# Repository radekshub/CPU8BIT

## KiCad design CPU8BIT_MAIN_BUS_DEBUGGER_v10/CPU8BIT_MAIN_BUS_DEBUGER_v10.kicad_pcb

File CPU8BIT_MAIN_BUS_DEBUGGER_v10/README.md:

CPU 8 bit - MAIN BUS DEBUGGER version 1.0

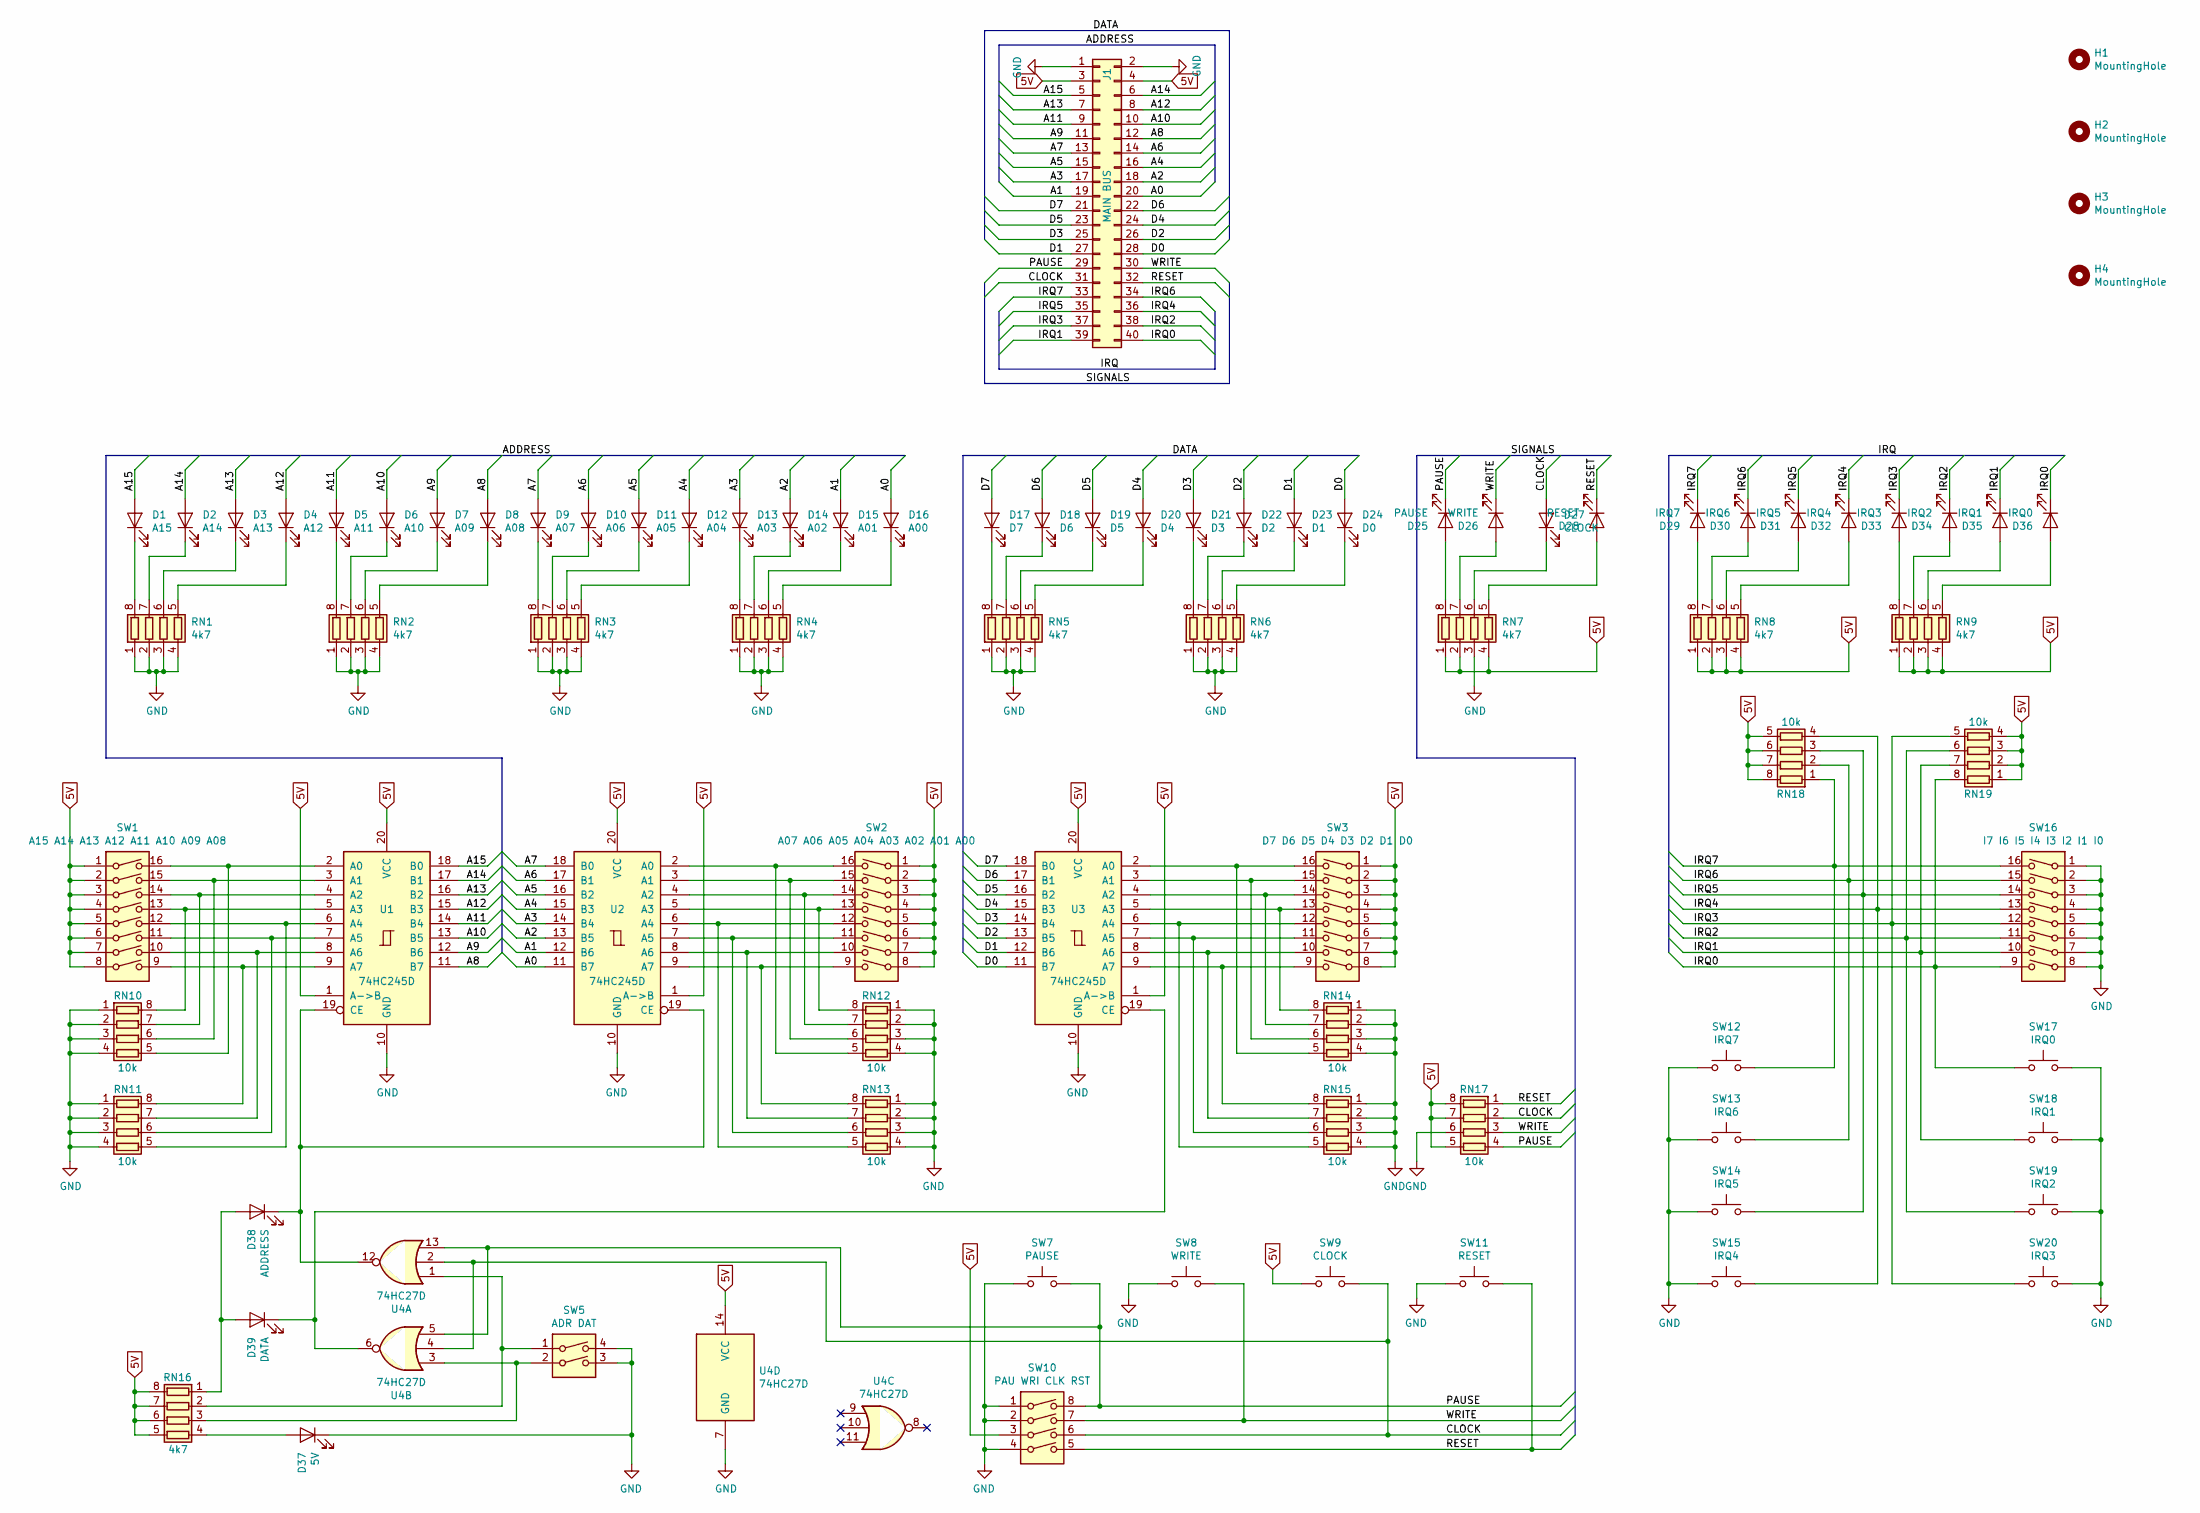
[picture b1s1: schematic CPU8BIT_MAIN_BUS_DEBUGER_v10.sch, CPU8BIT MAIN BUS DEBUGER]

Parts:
D1: A15; LED_0805_2012Metric_Pad1.15x1.40mm_HandSolder
D2: A14; LED_0805_2012Metric_Pad1.15x1.40mm_HandSolder
D3: A13; LED_0805_2012Metric_Pad1.15x1.40mm_HandSolder
D4: A12; LED_0805_2012Metric_Pad1.15x1.40mm_HandSolder
D5: A11; LED_0805_2012Metric_Pad1.15x1.40mm_HandSolder
D6: A10; LED_0805_2012Metric_Pad1.15x1.40mm_HandSolder
D7: A09; LED_0805_2012Metric_Pad1.15x1.40mm_HandSolder
D8: A08; LED_0805_2012Metric_Pad1.15x1.40mm_HandSolder
D9: A07; LED_0805_2012Metric_Pad1.15x1.40mm_HandSolder
D10: A06; LED_0805_2012Metric_Pad1.15x1.40mm_HandSolder
D11: A05; LED_0805_2012Metric_Pad1.15x1.40mm_HandSolder
D12: A04; LED_0805_2012Metric_Pad1.15x1.40mm_HandSolder
D13: A03; LED_0805_2012Metric_Pad1.15x1.40mm_HandSolder
D14: A02; LED_0805_2012Metric_Pad1.15x1.40mm_HandSolder
D15: A01; LED_0805_2012Metric_Pad1.15x1.40mm_HandSolder
D16: A00; LED_0805_2012Metric_Pad1.15x1.40mm_HandSolder
D17: D7; LED_0805_2012Metric_Pad1.15x1.40mm_HandSolder
D18: D6; LED_0805_2012Metric_Pad1.15x1.40mm_HandSolder
D19: D5; LED_0805_2012Metric_Pad1.15x1.40mm_HandSolder
D20: D4; LED_0805_2012Metric_Pad1.15x1.40mm_HandSolder
D21: D3; LED_0805_2012Metric_Pad1.15x1.40mm_HandSolder
D22: D2; LED_0805_2012Metric_Pad1.15x1.40mm_HandSolder
D23: D1; LED_0805_2012Metric_Pad1.15x1.40mm_HandSolder
D24: D0; LED_0805_2012Metric_Pad1.15x1.40mm_HandSolder
D25: PAUSE; LED_0805_2012Metric_Pad1.15x1.40mm_HandSolder
D26: WRITE; LED_0805_2012Metric_Pad1.15x1.40mm_HandSolder
D27: CLOCK; LED_0805_2012Metric_Pad1.15x1.40mm_HandSolder
D28: RESET; LED_0805_2012Metric_Pad1.15x1.40mm_HandSolder
D29: IRQ7; LED_0805_2012Metric_Pad1.15x1.40mm_HandSolder
D30: IRQ6; LED_0805_2012Metric_Pad1.15x1.40mm_HandSolder
D31: IRQ5; LED_0805_2012Metric_Pad1.15x1.40mm_HandSolder
D32: IRQ4; LED_0805_2012Metric_Pad1.15x1.40mm_HandSolder
D33: IRQ3; LED_0805_2012Metric_Pad1.15x1.40mm_HandSolder
D34: IRQ2; LED_0805_2012Metric_Pad1.15x1.40mm_HandSolder
D35: IRQ1; LED_0805_2012Metric_Pad1.15x1.40mm_HandSolder
D36: IRQ0; LED_0805_2012Metric_Pad1.15x1.40mm_HandSolder
D37: 5V; LED_0805_2012Metric_Pad1.15x1.40mm_HandSolder
D38: ADDRESS; LED_0805_2012Metric_Pad1.15x1.40mm_HandSolder
D39: DATA; LED_0805_2012Metric_Pad1.15x1.40mm_HandSolder
H1, H2, H3, H4: MountingHole; MountingHole_4.3mm_M4_Pad_Via
J1: MAIN BUS; PinHeader_2x20_P2.54mm_Horizontal
RN1, RN2, RN3, RN4, RN5, RN6, RN7, RN8, RN9, RN16: 4k7; R_Array_Convex_4x0603
RN10, RN11, RN12, RN13, RN14, RN15, RN17, RN18, RN19: 10k; R_Array_Convex_4x0603
SW1: A15 A14 A13 A12 A11 A10 A09 A08; SW_DIP_SPSTx08_Piano_10.8x21.88mm_W7.62mm_P2.54mm
SW2: A07 A06 A05 A04 A03 A02 A01 A00; SW_DIP_SPSTx08_Piano_10.8x21.88mm_W7.62mm_P2.54mm
SW3: D7 D6 D5 D4 D3 D2 D1 D0; SW_DIP_SPSTx08_Piano_10.8x21.88mm_W7.62mm_P2.54mm
SW5: ADR DAT; SW_DIP_SPSTx02_Piano_10.8x6.64mm_W7.62mm_P2.54mm
SW7: PAUSE; SW_PUSH_6mm
SW8: WRITE; SW_PUSH_6mm
SW9: CLOCK; SW_PUSH_6mm
SW10: PAU WRI CLK RST; SW_DIP_SPSTx04_Piano_10.8x11.72mm_W7.62mm_P2.54mm
SW11: RESET; SW_PUSH_6mm
SW12: IRQ7; SW_PUSH_6mm
SW13: IRQ6; SW_PUSH_6mm
SW14: IRQ5; SW_PUSH_6mm
SW15: IRQ4; SW_PUSH_6mm
SW16: I7 I6 I5 I4 I3 I2 I1 I0; SW_DIP_SPSTx08_Piano_10.8x21.88mm_W7.62mm_P2.54mm
SW17: IRQ0; SW_PUSH_6mm
SW18: IRQ1; SW_PUSH_6mm
SW19: IRQ2; SW_PUSH_6mm
SW20: IRQ3; SW_PUSH_6mm
U1, U2, U3: 74HC245D; SO-20_12.8x7.5mm_P1.27mm
U4: 74HC27D; SOIC-14_3.9x8.7mm_P1.27mm

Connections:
5V: J1.3, J1.4, RN7.1 (R1.1), RN7.2 (R2.1), RN7.4 (R4.1), RN8.1 (R1.1), RN8.2 (R2.1), RN8.3 (R3.1), RN8.4 (R4.1), RN9.1 (R1.1), RN9.2 (R2.1), RN9.3 (R3.1), RN9.4 (R4.1), RN16.5 (R4.2), RN16.6 (R3.2), RN16.7 (R2.2), RN16.8 (R1.2), RN17.5 (R4.2), RN17.7 (R2.2), RN17.8 (R1.2), RN18.5 (R4.2), RN18.6 (R3.2), RN18.7 (R2.2), RN18.8 (R1.2), RN19.1 (R1.1), RN19.2 (R2.1), RN19.3 (R3.1), RN19.4 (R4.1), SW1.1, SW1.2, SW1.3, SW1.4, SW1.5, SW1.6, SW1.7, SW1.8, SW2.1, SW2.2, SW2.3, SW2.4, SW2.5, SW2.6, SW2.7, SW2.8, SW3.1, SW3.2, SW3.3, SW3.4, SW3.5, SW3.6, SW3.7, SW3.8, SW9.1, SW10.3, U1.1 (A->B), U1.20 (VCC), U2.1 (A->B), U2.20 (VCC), U3.1 (A->B), U3.20 (VCC), U4.14 (VCC)
/A0: D16.2 (A), J1.20, U2.11 (B7)
/A1: D15.2 (A), J1.19, U2.12 (B6)
/A2: D14.2 (A), J1.18, U2.13 (B5)
/A3: D13.2 (A), J1.17, U2.14 (B4)
/A4: D12.2 (A), J1.16, U2.15 (B3)
/A5: D11.2 (A), J1.15, U2.16 (B2)
/A6: D10.2 (A), J1.14, U2.17 (B1)
/A7: D9.2 (A), J1.13, U2.18 (B0)
/A8: D8.2 (A), J1.12, U1.11 (B7)
/A9: D7.2 (A), J1.11, U1.12 (B6)
/A10: D6.2 (A), J1.10, U1.13 (B5)
/A11: D5.2 (A), J1.9, U1.14 (B4)
/A12: D4.2 (A), J1.8, U1.15 (B3)
/A13: D3.2 (A), J1.7, U1.16 (B2)
/A14: D2.2 (A), J1.6, U1.17 (B1)
/A15: D1.2 (A), J1.5, U1.18 (B0)
/CLOCK: D27.2 (A), J1.31, RN17.2 (R2.1), SW9.2, SW10.6, U4.2, U4.4
/D0: D24.2 (A), J1.28, U3.11 (B7)
/D1: D23.2 (A), J1.27, U3.12 (B6)
/D2: D22.2 (A), J1.26, U3.13 (B5)
/D3: D21.2 (A), J1.25, U3.14 (B4)
/D4: D20.2 (A), J1.24, U3.15 (B3)
/D5: D19.2 (A), J1.23, U3.16 (B2)
/D6: D18.2 (A), J1.22, U3.17 (B1)
/D7: D17.2 (A), J1.21, U3.18 (B0)
/IRQ0: D36.1 (K), J1.40, RN19.8 (R1.2), SW16.9, SW17.1
/IRQ1: D35.1 (K), J1.39, RN19.7 (R2.2), SW16.10, SW18.1
/IRQ2: D34.1 (K), J1.38, RN19.6 (R3.2), SW16.11, SW19.1
/IRQ3: D33.1 (K), J1.37, RN19.5 (R4.2), SW16.12, SW20.1
/IRQ4: D32.1 (K), J1.36, RN18.4 (R4.1), SW15.2, SW16.13
/IRQ5: D31.1 (K), J1.35, RN18.3 (R3.1), SW14.2, SW16.14
/IRQ6: D30.1 (K), J1.34, RN18.2 (R2.1), SW13.2, SW16.15
/IRQ7: D29.1 (K), J1.33, RN18.1 (R1.1), SW12.2, SW16.16
/PAUSE: D25.1 (K), J1.29, RN17.4 (R4.1), SW7.2, SW10.8, U4.5, U4.13
/RESET: D28.1 (K), J1.32, RN17.1 (R1.1), SW10.5, SW11.2
/WRITE: D26.1 (K), J1.30, RN17.3 (R3.1), SW8.2, SW10.7
GND: D37.1 (K), J1.1, J1.2, RN1.1 (R1.1), RN1.2 (R2.1), RN1.3 (R3.1), RN1.4 (R4.1), RN2.1 (R1.1), RN2.2 (R2.1), RN2.3 (R3.1), RN2.4 (R4.1), RN3.1 (R1.1), RN3.2 (R2.1), RN3.3 (R3.1), RN3.4 (R4.1), RN4.1 (R1.1), RN4.2 (R2.1), RN4.3 (R3.1), RN4.4 (R4.1), RN5.1 (R1.1), RN5.2 (R2.1), RN5.3 (R3.1), RN5.4 (R4.1), RN6.1 (R1.1), RN6.2 (R2.1), RN6.3 (R3.1), RN6.4 (R4.1), RN7.3 (R3.1), RN10.1 (R1.1), RN10.2 (R2.1), RN10.3 (R3.1), RN10.4 (R4.1), RN11.1 (R1.1), RN11.2 (R2.1), RN11.3 (R3.1), RN11.4 (R4.1), RN12.1 (R1.1), RN12.2 (R2.1), RN12.3 (R3.1), RN12.4 (R4.1), RN13.1 (R1.1), RN13.2 (R2.1), RN13.3 (R3.1), RN13.4 (R4.1), RN14.1 (R1.1), RN14.2 (R2.1), RN14.3 (R3.1), RN14.4 (R4.1), RN15.1 (R1.1), RN15.2 (R2.1), RN15.3 (R3.1), RN15.4 (R4.1), RN17.6 (R3.2), SW5.3, SW5.4, SW7.1, SW8.1, SW10.1, SW10.2, SW10.4, SW11.1, SW12.1, SW13.1, SW14.1, SW15.1, SW16.1, SW16.2, SW16.3, SW16.4, SW16.5, SW16.6, SW16.7, SW16.8, SW17.2, SW18.2, SW19.2, SW20.2, U1.10 (GND), U2.10 (GND), U3.10 (GND), U4.7 (GND)
unnamed: D1.1 (K), RN1.8 (R1.2)
unnamed: D2.1 (K), RN1.7 (R2.2)
unnamed: D3.1 (K), RN1.6 (R3.2)
unnamed: D4.1 (K), RN1.5 (R4.2)
unnamed: D5.1 (K), RN2.8 (R1.2)
unnamed: D6.1 (K), RN2.7 (R2.2)
unnamed: D7.1 (K), RN2.6 (R3.2)
unnamed: D8.1 (K), RN2.5 (R4.2)
unnamed: D9.1 (K), RN3.8 (R1.2)
unnamed: D10.1 (K), RN3.7 (R2.2)
unnamed: D11.1 (K), RN3.6 (R3.2)
unnamed: D12.1 (K), RN3.5 (R4.2)
unnamed: D13.1 (K), RN4.8 (R1.2)
unnamed: D14.1 (K), RN4.7 (R2.2)
unnamed: D15.1 (K), RN4.6 (R3.2)
unnamed: D16.1 (K), RN4.5 (R4.2)
unnamed: D17.1 (K), RN5.8 (R1.2)
unnamed: D18.1 (K), RN5.7 (R2.2)
unnamed: D19.1 (K), RN5.6 (R3.2)
unnamed: D20.1 (K), RN5.5 (R4.2)
unnamed: D21.1 (K), RN6.8 (R1.2)
unnamed: D22.1 (K), RN6.7 (R2.2)
unnamed: D23.1 (K), RN6.6 (R3.2)
unnamed: D24.1 (K), RN6.5 (R4.2)
unnamed: D25.2 (A), RN7.8 (R1.2)
unnamed: D26.2 (A), RN7.7 (R2.2)
unnamed: D27.1 (K), RN7.6 (R3.2)
unnamed: D28.2 (A), RN7.5 (R4.2)
unnamed: D29.2 (A), RN8.8 (R1.2)
unnamed: D30.2 (A), RN8.7 (R2.2)
unnamed: D31.2 (A), RN8.6 (R3.2)
unnamed: D32.2 (A), RN8.5 (R4.2)
unnamed: D33.2 (A), RN9.8 (R1.2)
unnamed: D34.2 (A), RN9.7 (R2.2)
unnamed: D35.2 (A), RN9.6 (R3.2)
unnamed: D36.2 (A), RN9.5 (R4.2)
unnamed: D37.2 (A), RN16.4 (R4.1)
unnamed: D38.1 (K), U1.19 (CE), U2.19 (CE), U4.12
unnamed: D38.2 (A), D39.2 (A), RN16.1 (R1.1)
unnamed: D39.1 (K), U3.19 (CE), U4.6
unnamed: RN10.5 (R4.2), SW1.16, U1.2 (A0)
unnamed: RN10.6 (R3.2), SW1.15, U1.3 (A1)
unnamed: RN10.7 (R2.2), SW1.14, U1.4 (A2)
unnamed: RN10.8 (R1.2), SW1.13, U1.5 (A3)
unnamed: RN11.5 (R4.2), SW1.12, U1.6 (A4)
unnamed: RN11.6 (R3.2), SW1.11, U1.7 (A5)
unnamed: RN11.7 (R2.2), SW1.10, U1.8 (A6)
unnamed: RN11.8 (R1.2), SW1.9, U1.9 (A7)
unnamed: RN12.5 (R4.2), SW2.16, U2.2 (A0)
unnamed: RN12.6 (R3.2), SW2.15, U2.3 (A1)
unnamed: RN12.7 (R2.2), SW2.14, U2.4 (A2)
unnamed: RN12.8 (R1.2), SW2.13, U2.5 (A3)
unnamed: RN13.5 (R4.2), SW2.12, U2.6 (A4)
unnamed: RN13.6 (R3.2), SW2.11, U2.7 (A5)
unnamed: RN13.7 (R2.2), SW2.10, U2.8 (A6)
unnamed: RN13.8 (R1.2), SW2.9, U2.9 (A7)
unnamed: RN14.5 (R4.2), SW3.16, U3.2 (A0)
unnamed: RN14.6 (R3.2), SW3.15, U3.3 (A1)
unnamed: RN14.7 (R2.2), SW3.14, U3.4 (A2)
unnamed: RN14.8 (R1.2), SW3.13, U3.5 (A3)
unnamed: RN15.5 (R4.2), SW3.12, U3.6 (A4)
unnamed: RN15.6 (R3.2), SW3.11, U3.7 (A5)
unnamed: RN15.7 (R2.2), SW3.10, U3.8 (A6)
unnamed: RN15.8 (R1.2), SW3.9, U3.9 (A7)
unnamed: RN16.2 (R2.1), SW5.1, U4.1
unnamed: RN16.3 (R3.1), SW5.2, U4.3

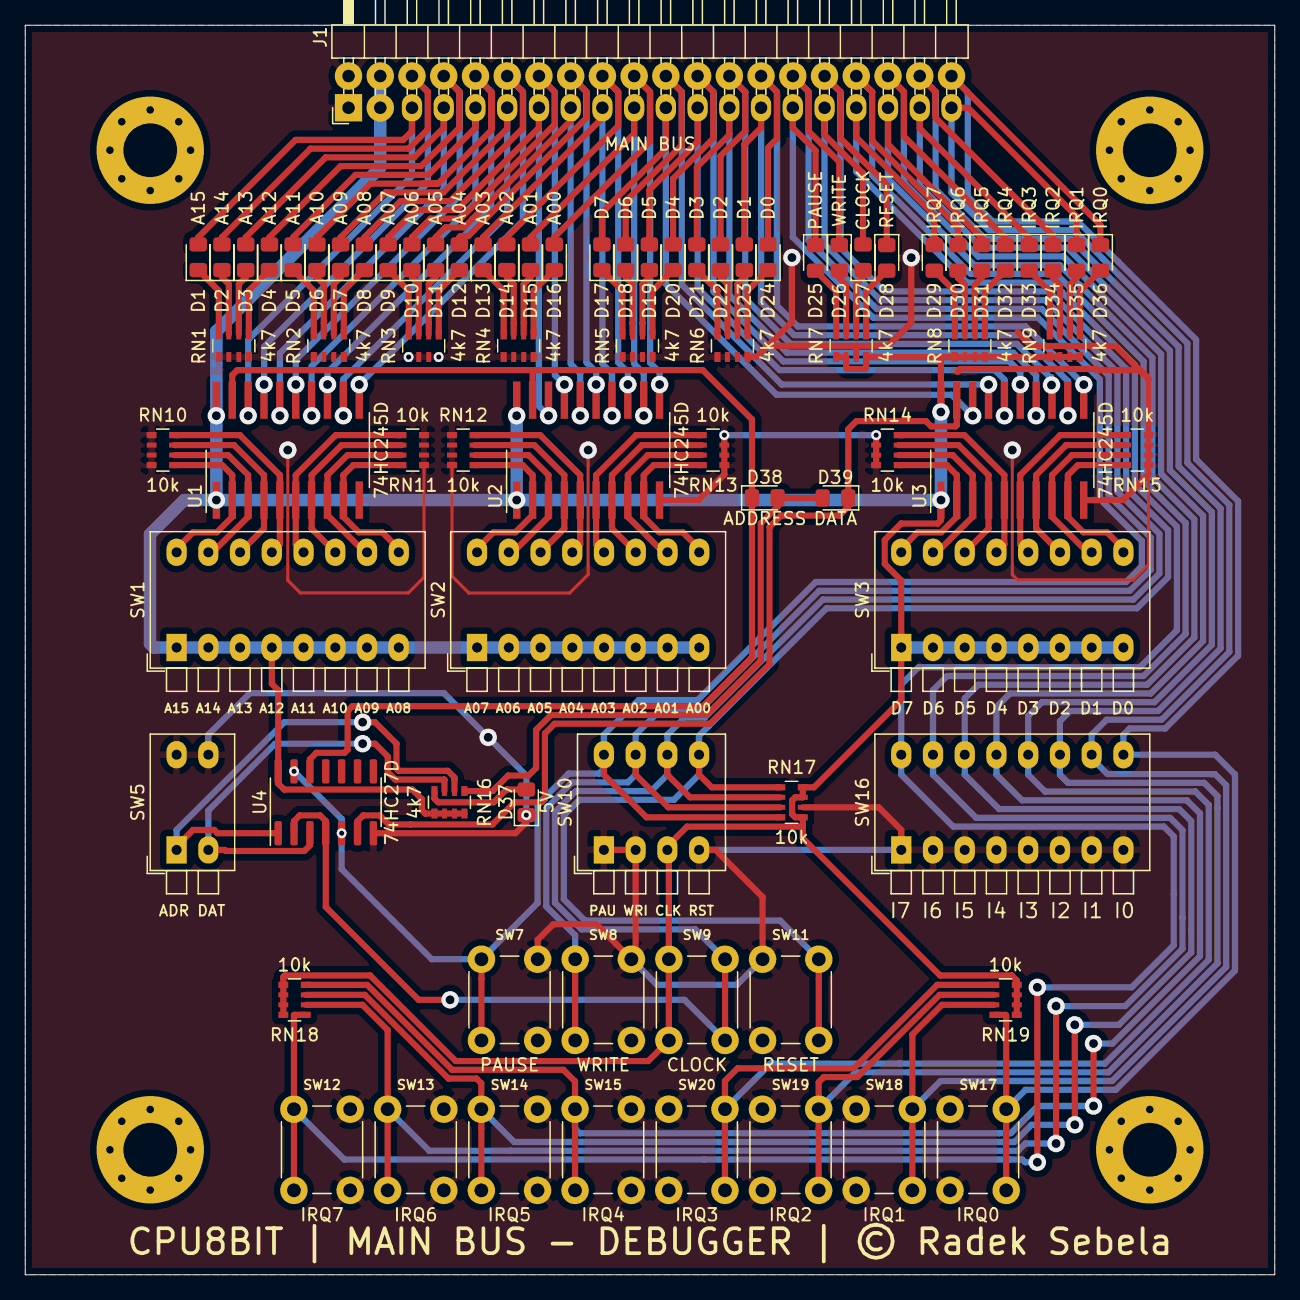
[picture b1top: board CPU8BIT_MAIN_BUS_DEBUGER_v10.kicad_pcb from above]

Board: 2 copper layers, 100.0 x 100.0 mm, 85 parts (0 on the bottom side), 104 nets.

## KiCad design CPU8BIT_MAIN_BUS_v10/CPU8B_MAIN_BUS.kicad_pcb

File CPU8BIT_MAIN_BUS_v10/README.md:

# CPU8BIT_MAIN_BUS_v10
CPU 8 bit - MAIN BUS version 1.0

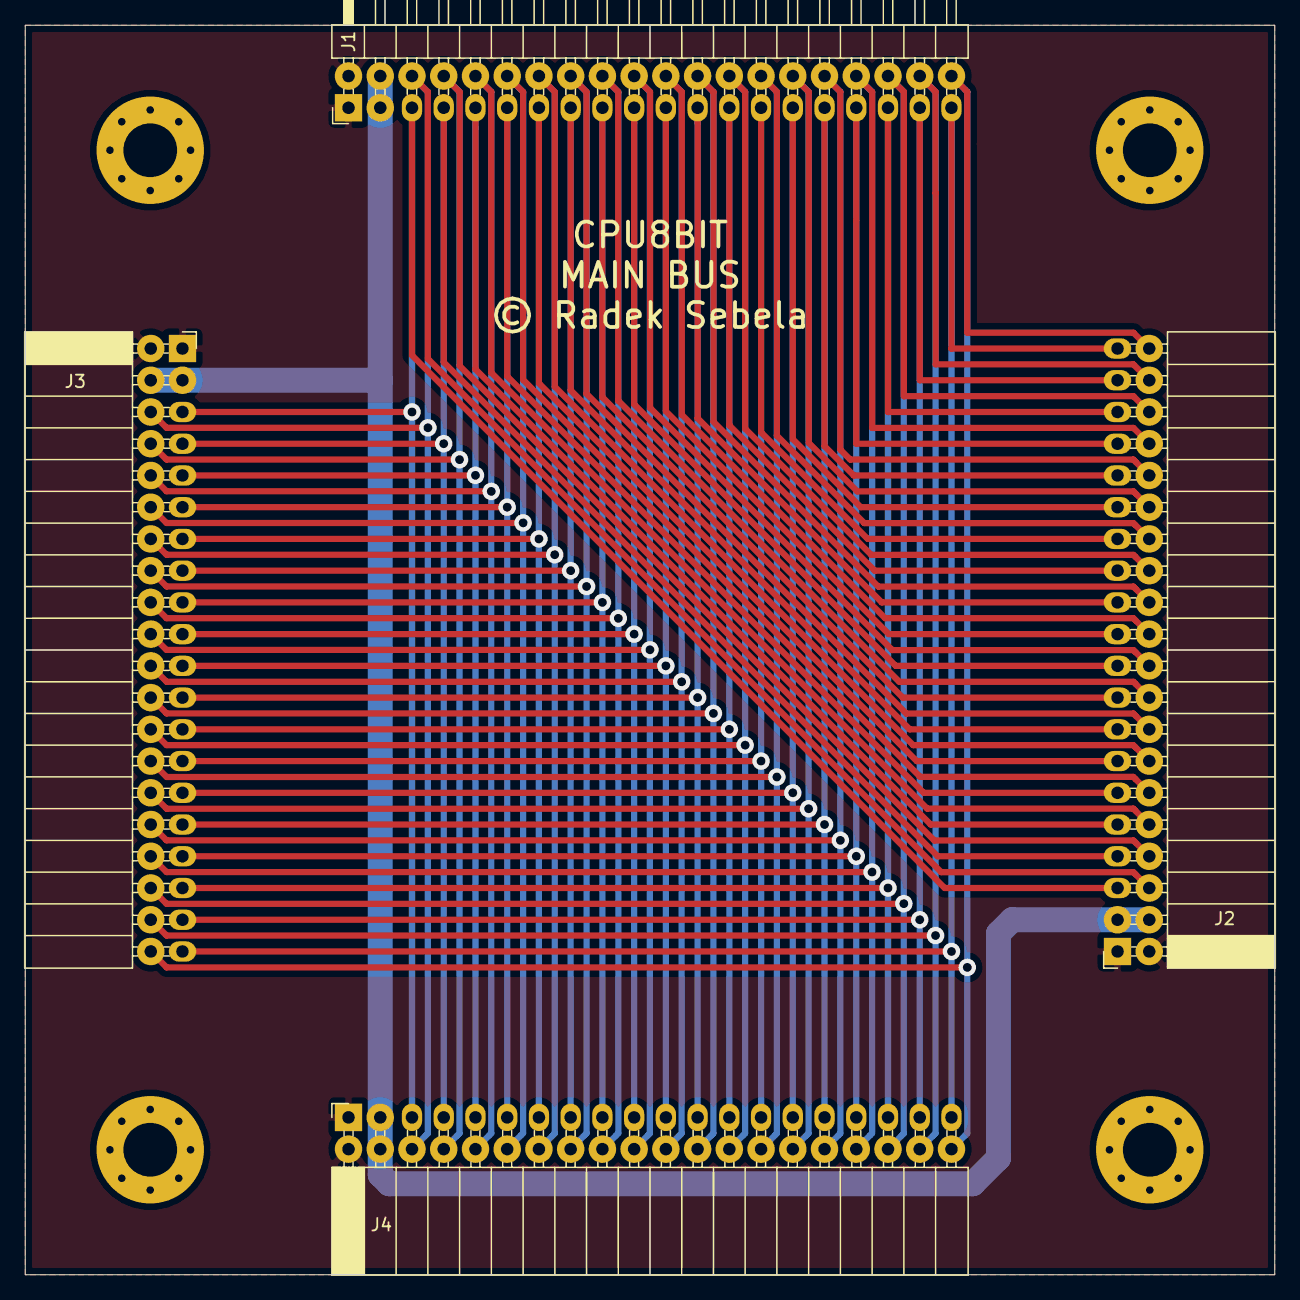
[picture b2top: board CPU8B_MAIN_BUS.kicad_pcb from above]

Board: 2 copper layers, 100.0 x 100.0 mm, 4 parts (0 on the bottom side), 38 nets.

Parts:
J1: Conn_02x20_Odd_Even; PinHeader_2x20_P2.54mm_Horizontal
J2, J3, J4: Conn_02x20_Odd_Even; PinSocket_2x20_P2.54mm_Horizontal

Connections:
GND: J1.1, J1.2, J2.1, J2.2, J3.1, J3.2, J4.1, J4.2
unnamed: J1.3, J1.4, J2.3, J2.4, J3.3, J3.4, J4.3, J4.4
unnamed: J1.5, J2.5, J3.5, J4.5
unnamed: J1.6, J2.6, J3.6, J4.6
unnamed: J1.7, J2.7, J3.7, J4.7
unnamed: J1.8, J2.8, J3.8, J4.8
unnamed: J1.9, J2.9, J3.9, J4.9
unnamed: J1.10, J2.10, J3.10, J4.10
unnamed: J1.11, J2.11, J3.11, J4.11
unnamed: J1.12, J2.12, J3.12, J4.12
unnamed: J1.13, J2.13, J3.13, J4.13
unnamed: J1.14, J2.14, J3.14, J4.14
unnamed: J1.15, J2.15, J3.15, J4.15
unnamed: J1.16, J2.16, J3.16, J4.16
unnamed: J1.17, J2.17, J3.17, J4.17
unnamed: J1.18, J2.18, J3.18, J4.18
unnamed: J1.19, J2.19, J3.19, J4.19
unnamed: J1.20, J2.20, J3.20, J4.20
unnamed: J1.21, J2.21, J3.21, J4.21
unnamed: J1.22, J2.22, J3.22, J4.22
unnamed: J1.23, J2.23, J3.23, J4.23
unnamed: J1.24, J2.24, J3.24, J4.24
unnamed: J1.25, J2.25, J3.25, J4.25
unnamed: J1.26, J2.26, J3.26, J4.26
unnamed: J1.27, J2.27, J3.27, J4.27
unnamed: J1.28, J2.28, J3.28, J4.28
unnamed: J1.29, J2.29, J3.29, J4.29
unnamed: J1.30, J2.30, J3.30, J4.30
unnamed: J1.31, J2.31, J3.31, J4.31
unnamed: J1.32, J2.32, J3.32, J4.32
unnamed: J1.33, J2.33, J3.33, J4.33
unnamed: J1.34, J2.34, J3.34, J4.34
unnamed: J1.35, J2.35, J3.35, J4.35
unnamed: J1.36, J2.36, J3.36, J4.36
unnamed: J1.37, J2.37, J3.37, J4.37
unnamed: J1.38, J2.38, J3.38, J4.38
unnamed: J1.39, J2.39, J3.39, J4.39
unnamed: J1.40, J2.40, J3.40, J4.40

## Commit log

2020-11-15 CPU8BIT_MAIN_BUS_v10 files were added.
2020-11-15 Fabrication files were added.
2020-11-15 CPU8BIT_MAIN_BUS_v10: Bottom and front images were added.

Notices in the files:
CPU8BIT_MAIN_BUS_DEBUGGER_v10/CPU8BIT_MAIN_BUS_DEBUGER_v10.kicad_pcb:
CPU8BIT | MAIN BUS - DEBUGGER | © Radek Sebela
